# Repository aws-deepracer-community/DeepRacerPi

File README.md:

# Introducing the DeepRacer Pi: A Budget-Friendly Compute Module Replacement for AWS DeepRacer

The **DeepRacer Pi** is a custom-designed PCB that serves as a cost-effective replacement for the original AWS DeepRacer compute module. With a production and assembly cost of just **$33**, the DeepRacer Pi brings the power of the **Raspberry Pi Compute Module 4 (CM4)** and the upcoming **Compute Module 5 (CM5)** to your DIY racing projects.

## What You Need
To get started with the DeepRacer Pi, you’ll need:
1. **Raspberry Pi CM4 Lite**: 
2. **SD Card**: 
3. **PiCamera V2**:

---

The DeepRacer Pi empowers makers and students to build, modify, and innovate with their AWS DeepRacer cars. it is a small enough package to fit into 1/28th scale car significantly reducing the footprint needed for AWS DeepRacer.

## TODO for DeepRacer Pi Development
1. **Move Camera and unneeded headers**
   - remove the extra header not needed for the servo control
   - move the camera next to the headers to face forward

2. **Implement Battery Monitor**  
   - Add circuitry and software support to monitor battery voltage and health.
   - Display battery status in real-time for improved usability.

3. **Fix USB OTG Support**  
   - Modify USB configuration to enable OTG (On-The-Go) functionality.
   - Ensure compatibility with peripherals and reliable data transfer.
4. **Add Tail light LED**
   - Implement multicolor Tail light indicator
5. **Add Fan header**
   - Enable FAN for additional cooling support
6. **Add UART via serial connector headers**
   - to enable additional debugging

## Setting Up the board

1. **Image SD card with  Ubuntu 22.04**
   - use win+shift+x to enable SSH and Wifi during imaging process
   - Edit /boot/firmware/config.txt
     - Add dtparam=i2c_arm=on
     - Add Start_x=1
     - Add dtoverlay=vc4-fkms-v3d
2. Follow these instructions
   - https://github.com/aws-deepracer-community/deepracer-custom-car

Special Thanks for Lars for all the work he did on the Deepracer-custom-car repo to make this a possibility!

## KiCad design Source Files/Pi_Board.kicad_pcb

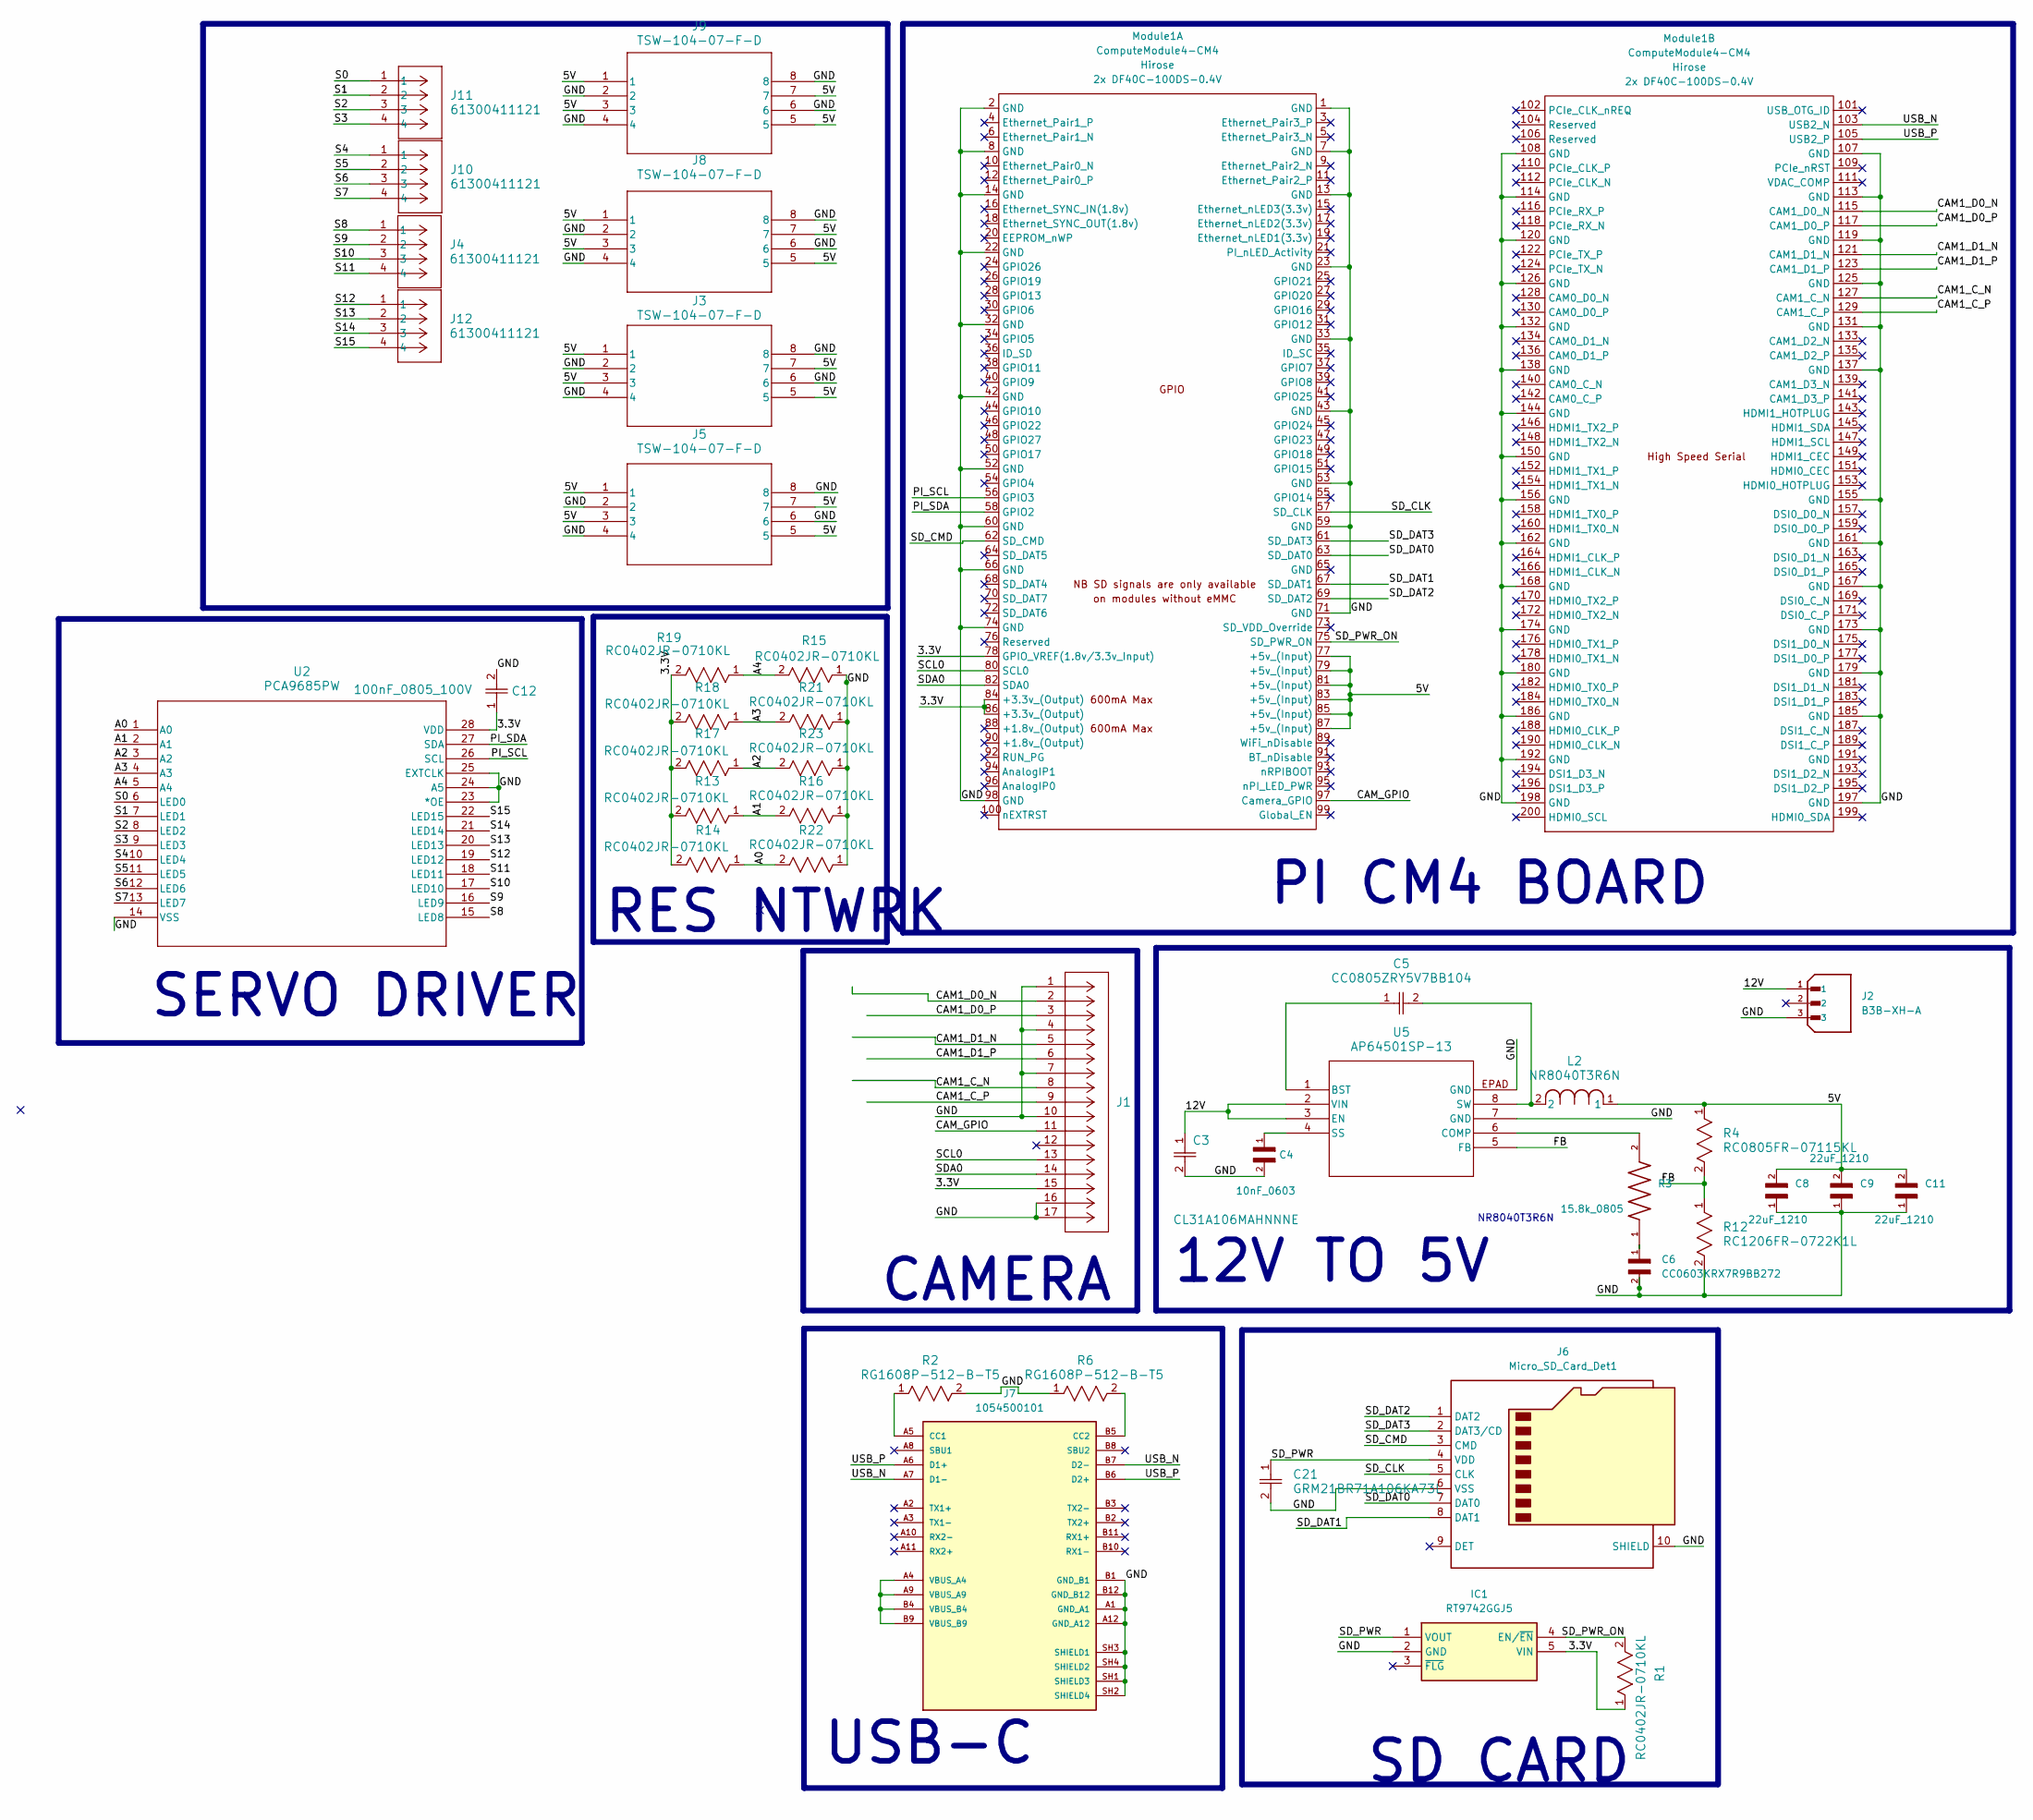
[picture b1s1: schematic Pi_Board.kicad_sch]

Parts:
C3: CL31A106MAHNNNE; CAP_CL31_SAM; Part Number CL31A106MAHNNNE
C4: 10nF_0603; CAPC1608X90
C5: CC0805ZRY5V7BB104; CAP_CC0805_YAG-L
C6: CC0603KRX7R9BB272; CAPC1608X90; Part Number CC0603KRX7R9BB272
C8, C9, C11: 22uF_1210; CAPC3225X270N
C12: 100nF_0805_100V; RC0805N_YAG
C21: GRM21BR71A106KA73L; CAP_GRM21_2p15X1p4X1p4_MUR; Part Number GRM21BR71A106KA73L
IC1: RT9742GGJ5; SOT94P280X100-5N; Mouser Part Number 835-RT9742GGJ5
J1: 15 Pin; CON15_1X15_DRB_SFW_FCI; Part Number SFW15R-2STE1LF
J2: B3B-XH-A; JST_B3B-XH-A; PARTREV 7/4/21
J3, J5, J8, J9: TSW-104-07-F-D; TSW-104-07-G-D_SAI
J4, J10, J11, J12: 61300411121; CONN_61300411121_WRE
J6: Micro_SD_Card_Det1; SDCARD_MOLEX_503398-1892
J7: 1054500101; MOLEX_1054500101; PARTREV A7
L2: NR8040T3R6N; IND_TAIYO_NR8040_TAY; Part Number NR8040T3R6N
Module1: ComputeModule4-CM4; Raspberry-Pi-4-Compute-Module
R1, R13, R14, R15, R16, R17, R18, R19, R21, R22, R23: RC0402JR-0710KL; RC0402N_YAG
R2, R6: RG1608P-512-B-T5; RES_0816_SUS
R3: 15.8k_0805; RESC2012X60N
R4: RC0805FR-07115KL; RC0805N_YAG-M
R12: RC1206FR-0722K1L; RC1206N_YAG-L
U2: PCA9685PW; SOT361-1_NXP-M
U5: AP64501SP-13; SO-8EP_DIO

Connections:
/3.3V: C12.1, IC1.5 (VIN), J1.15, Module1.78 (GPIO_VREF(1.8v/3.3v_Input)), Module1.84 (+3.3v_(Output)), Module1.86 (+3.3v_(Output)), R1.1, R13.2, R14.2, R17.2, R18.2, R19.2, U2.28 (VDD)
/5V: C8.2, C9.2, C11.2, J3.1, J3.3, J3.5, J3.7, J5.1, J5.3, J5.5, J5.7, J8.1, J8.3, J8.5, J8.7, J9.1, J9.3, J9.5, J9.7, L2.1, Module1.77 (+5v_(Input)), Module1.79 (+5v_(Input)), Module1.81 (+5v_(Input)), Module1.83 (+5v_(Input)), Module1.85 (+5v_(Input)), Module1.87 (+5v_(Input)), R4.1
/12V: C3.1, J2.1, U5.2 (VIN), U5.3 (EN)
/A0: R14.1, R22.2, U2.1 (A0)
/A1: R13.1, R16.2, U2.2 (A1)
/A2: R17.1, R23.2, U2.3 (A2)
/A3: R18.1, R21.2, U2.4 (A3)
/A4: R15.2, R19.1, U2.5 (A4)
/CAM1_C_N: J1.8, Module1.127 (CAM1_C_N)
/CAM1_C_P: J1.9, Module1.129 (CAM1_C_P)
/CAM1_D0_N: J1.2, Module1.115 (CAM1_D0_N)
/CAM1_D0_P: J1.3, Module1.117 (CAM1_D0_P)
/CAM1_D1_N: J1.5, Module1.121 (CAM1_D1_N)
/CAM1_D1_P: J1.6, Module1.123 (CAM1_D1_P)
/CAM_GPIO: J1.11, Module1.97 (Camera_GPIO)
/FB: R4.2, R12.1, U5.5 (FB)
/GND: C3.2, C4.2, C6.2, C8.1, C9.1, C11.1, C12.2, C21.2, IC1.2 (GND), J1.1, J1.4, J1.7, J1.10, J1.16, J1.17, J2.3, J3.2, J3.4, J3.6, J3.8, J5.2, J5.4, J5.6, J5.8, J6.6 (VSS), J6.10 (SHIELD), J7.A1 (GND_A1), J7.A12 (GND_A12), J7.B1 (GND_B1), J7.B12 (GND_B12), J7.SH1 (SHIELD3), J7.SH2 (SHIELD4), J7.SH3 (SHIELD1), J7.SH4 (SHIELD2), J8.2, J8.4, J8.6, J8.8, J9.2, J9.4, J9.6, J9.8, Module1.1 (GND), Module1.2 (GND), Module1.7 (GND), Module1.8 (GND), Module1.13 (GND), Module1.14 (GND), Module1.22 (GND), Module1.23 (GND), Module1.32 (GND), Module1.33 (GND), Module1.42 (GND), Module1.43 (GND), Module1.52 (GND), Module1.53 (GND), Module1.59 (GND), Module1.60 (GND), Module1.66 (GND), Module1.71 (GND), Module1.74 (GND), Module1.98 (GND), Module1.107 (GND), Module1.108 (GND), Module1.113 (GND), Module1.114 (GND), Module1.119 (GND), Module1.120 (GND), Module1.125 (GND), Module1.126 (GND), Module1.131 (GND), Module1.132 (GND), Module1.137 (GND), Module1.138 (GND), Module1.144 (GND), Module1.150 (GND), Module1.155 (GND), Module1.156 (GND), Module1.161 (GND), Module1.162 (GND), Module1.167 (GND), Module1.168 (GND), Module1.173 (GND), Module1.174 (GND), Module1.179 (GND), Module1.180 (GND), Module1.185 (GND), Module1.186 (GND), Module1.192 (GND), Module1.197 (GND), Module1.198 (GND), R2.2, R6.1, R12.2, R15.1, R16.1, R21.1, R22.1, R23.1, U2.14 (VSS), U2.23 (*OE), U2.24 (A5), U2.25 (EXTCLK), U5.7 (GND), U5.EPAD (GND)
/PI_SCL: Module1.56 (GPIO3), U2.26 (SCL)
/PI_SDA: Module1.58 (GPIO2), U2.27 (SDA)
/S0: J11.1, U2.6 (LED0)
/S1: J11.2, U2.7 (LED1)
/S2: J11.3, U2.8 (LED2)
/S3: J11.4, U2.9 (LED3)
/S4: J10.1, U2.10 (LED4)
/S5: J10.2, U2.11 (LED5)
/S6: J10.3, U2.12 (LED6)
/S7: J10.4, U2.13 (LED7)
/S8: J4.1, U2.15 (LED8)
/S9: J4.2, U2.16 (LED9)
/S10: J4.3, U2.17 (LED10)
/S11: J4.4, U2.18 (LED11)
/S12: J12.1, U2.19 (LED12)
/S13: J12.2, U2.20 (LED13)
/S14: J12.3, U2.21 (LED14)
/S15: J12.4, U2.22 (LED15)
/SCL0: J1.13, Module1.80 (SCL0)
/SDA0: J1.14, Module1.82 (SDA0)
/SD_CLK: J6.5 (CLK), Module1.57 (SD_CLK)
/SD_CMD: J6.3 (CMD), Module1.62 (SD_CMD)
/SD_DAT0: J6.7 (DAT0), Module1.63 (SD_DAT0)
/SD_DAT1: J6.8 (DAT1), Module1.67 (SD_DAT1)
/SD_DAT2: J6.1 (DAT2), Module1.69 (SD_DAT2)
/SD_DAT3: J6.2 (DAT3/CD), Module1.61 (SD_DAT3)
/SD_PWR: C21.1, IC1.1 (VOUT), J6.4 (VDD)
/SD_PWR_ON: IC1.4 (EN/~EN), Module1.75 (SD_PWR_ON), R1.2
/USB_N: J7.A7 (D1-), J7.B7 (D2-), Module1.103 (USB2_N)
/USB_P: J7.A6 (D1+), J7.B6 (D2+), Module1.105 (USB2_P)
unnamed: C6.1, R3.1
unnamed: J7.A5 (CC1), R2.1
unnamed: J7.B5 (CC2), R6.2
unnamed: J7.A4 (VBUS_A4), J7.A9 (VBUS_A9), J7.B4 (VBUS_B4), J7.B9 (VBUS_B9)
unnamed: C5.1, U5.1 (BST)
unnamed: R3.2, U5.6 (COMP)
unnamed: C4.1, U5.4 (SS)
unnamed: C5.2, L2.2, U5.8 (SW)

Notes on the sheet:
SD CARD
NR8040T3R6N
SERVO DRIVER
PI CM4 BOARD
12V TO 5V
CAMERA
USB-C
RES NTWRK

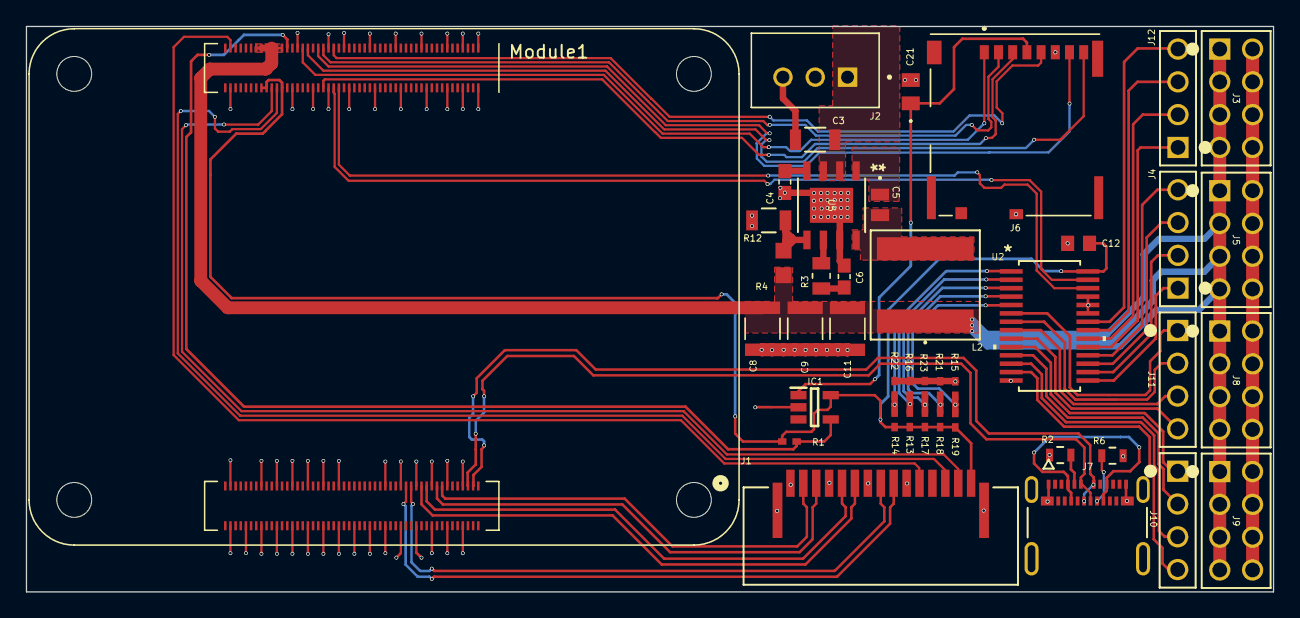
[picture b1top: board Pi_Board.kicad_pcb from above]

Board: 2 copper layers, 96.6 x 43.8 mm, 42 parts (0 on the bottom side), 55 nets.

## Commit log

2025-01-15 Update LICENSE
2025-01-15 PiRacerV1
2025-01-15 added images
2025-01-15 image resize
2025-01-15 updated todo
2025-01-15 updated readme format
2025-01-15 added additional image
